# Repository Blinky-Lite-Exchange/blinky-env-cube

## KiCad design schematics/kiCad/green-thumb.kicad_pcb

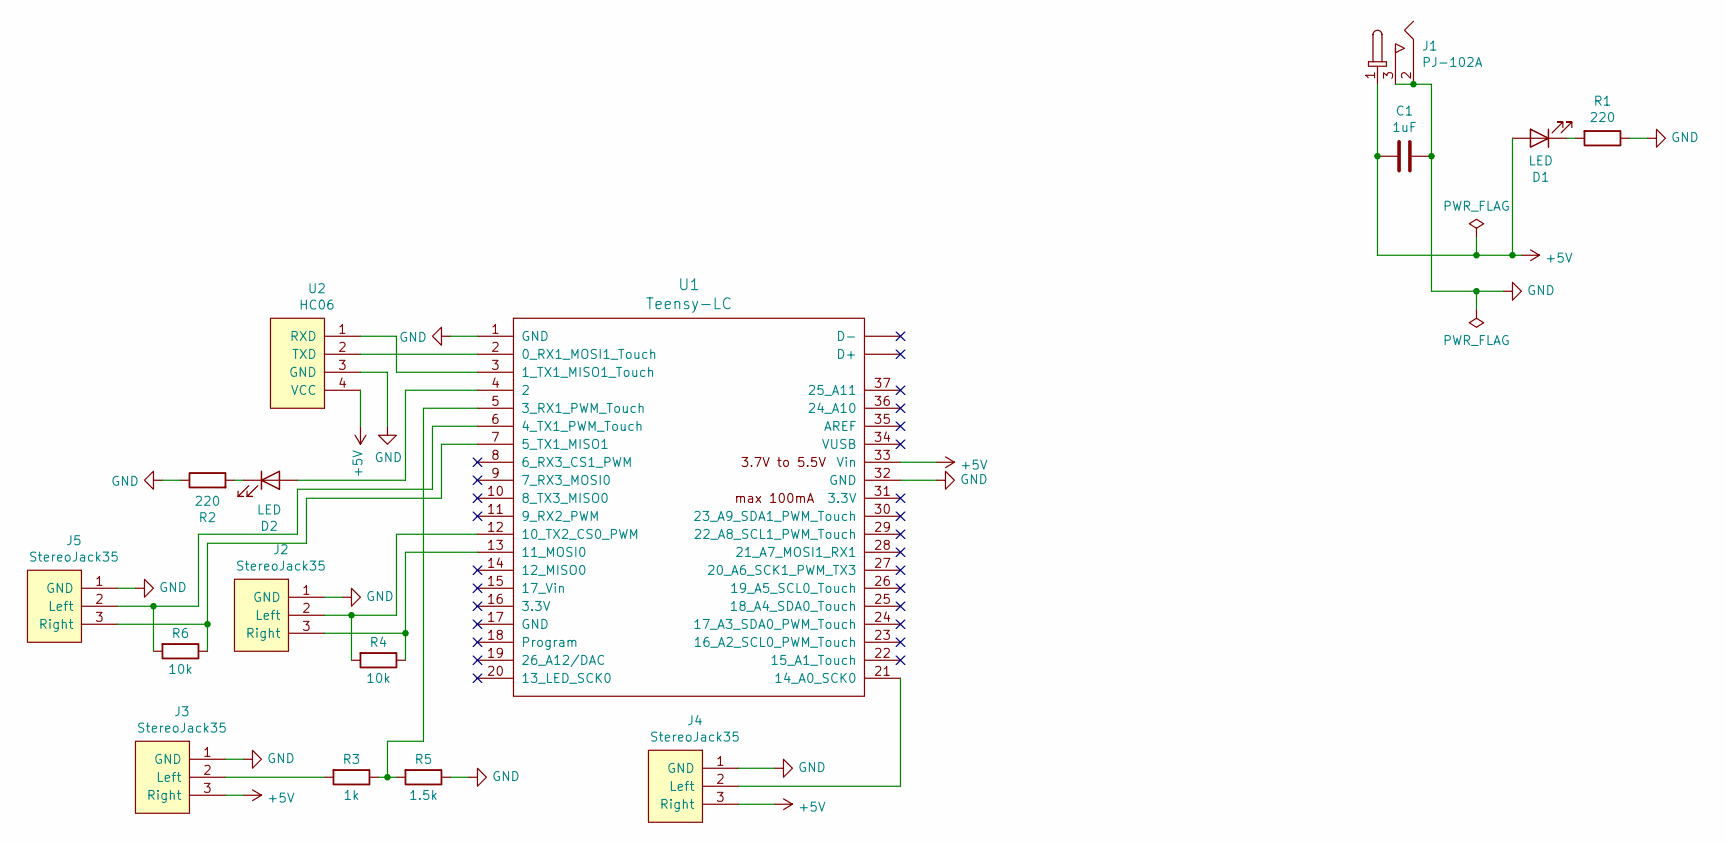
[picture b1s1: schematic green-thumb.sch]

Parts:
C1: 1uF; C_1206_3216Metric_Pad1.42x1.75mm_HandSolder
D1, D2: LED; LED_D5.0mm
J1: PJ-102A; DC21Jack
J2, J3, J4, J5: StereoJack35
R1, R2: 220; R_1206_3216Metric_Pad1.42x1.75mm_HandSolder
R3: 1k; R_1206_3216Metric_Pad1.42x1.75mm_HandSolder
R4, R6: 10k; R_1206_3216Metric_Pad1.42x1.75mm_HandSolder
R5: 1.5k; R_1206_3216Metric_Pad1.42x1.75mm_HandSolder
U1: Teensy-LC; Teensy30_31_32_LC
U2: HC06

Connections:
+5V: C1.2, D1.2 (A), J1.1, J3.3 (Right), J4.3 (Right), U1.33 (Vin), U2.4 (VCC)
GND: C1.1, J1.2, J1.3, J2.1 (GND), J3.1 (GND), J4.1 (GND), J5.1 (GND), R1.1, R2.1, R5.1, U1.1 (GND), U1.32 (GND), U2.3 (GND)
unnamed: D1.1 (K), R1.2
unnamed: D2.1 (K), R2.2
unnamed: D2.2 (A), U1.4 (2)
unnamed: J2.2 (Left), R4.2, U1.12 (10_TX2_CS0_PWM)
unnamed: J2.3 (Right), R4.1, U1.13 (11_MOSI0)
unnamed: J3.2 (Left), R3.2
unnamed: J4.2 (Left), U1.21 (14_A0_SCK0)
unnamed: J5.2 (Left), R6.2, U1.6 (4_TX1_PWM_Touch)
unnamed: J5.3 (Right), R6.1, U1.7 (5_TX1_MISO1)
unnamed: R3.1, R5.2, U1.5 (3_RX1_PWM_Touch)
unnamed: U1.2 (0_RX1_MOSI1_Touch), U2.2 (TXD)
unnamed: U1.3 (1_TX1_MISO1_Touch), U2.1 (RXD)

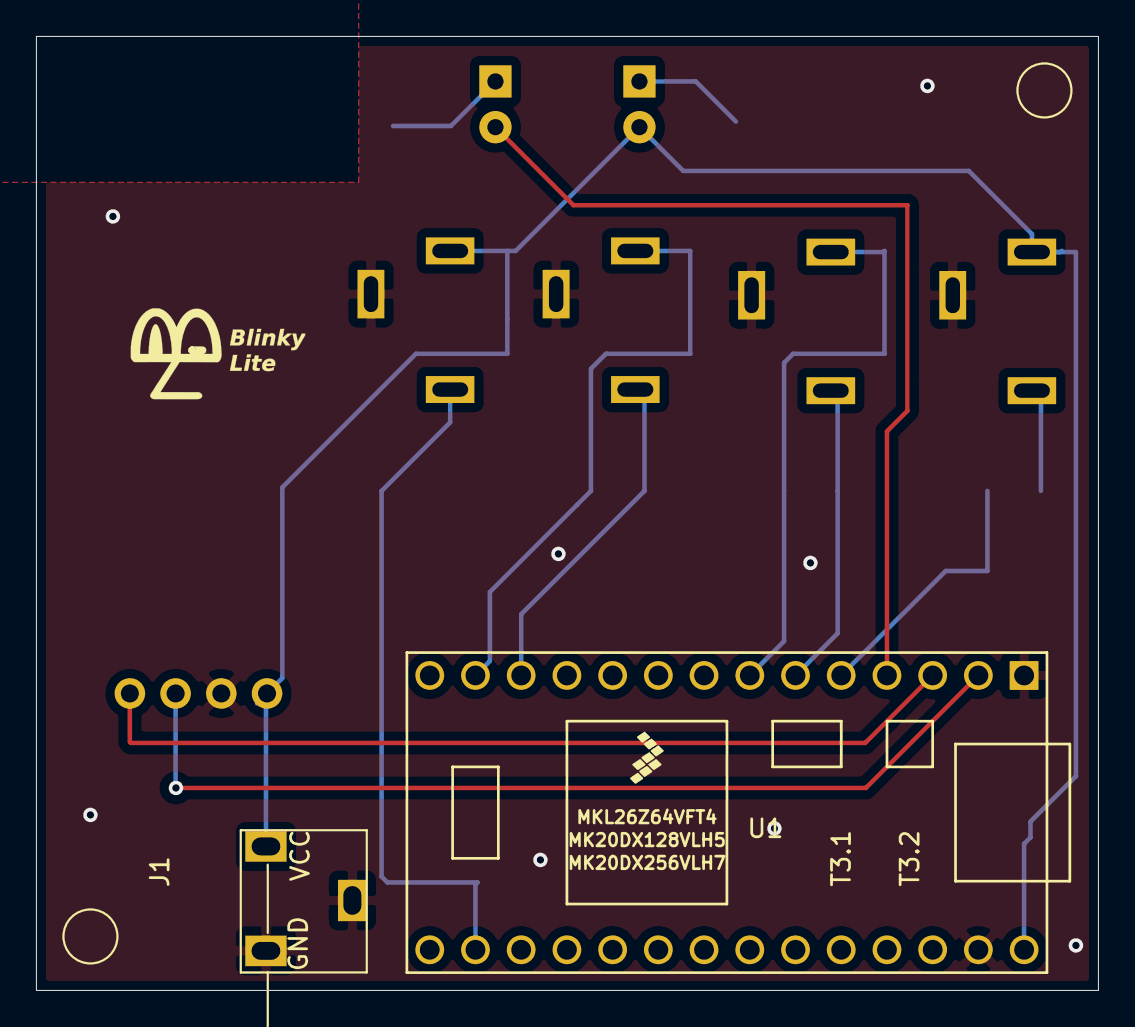
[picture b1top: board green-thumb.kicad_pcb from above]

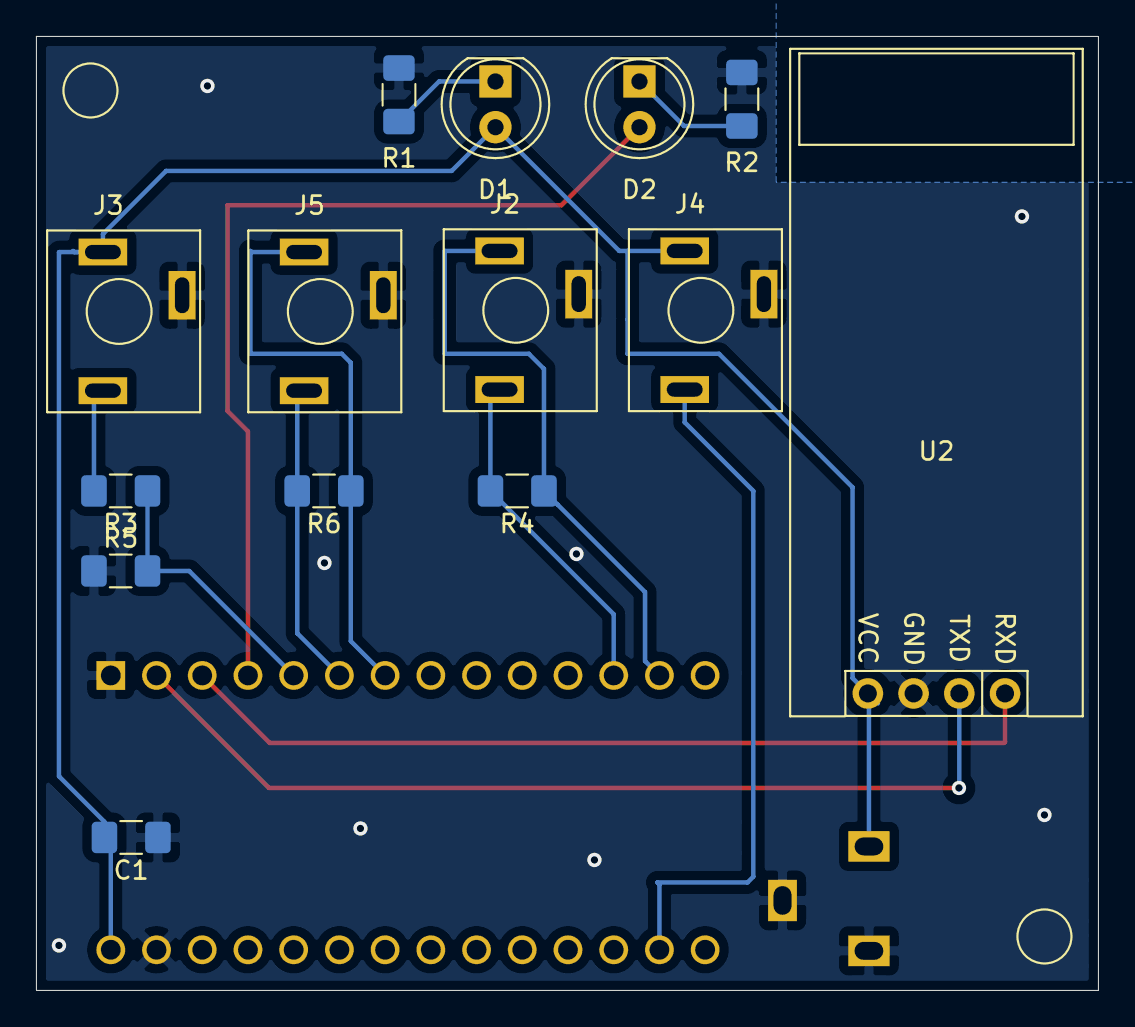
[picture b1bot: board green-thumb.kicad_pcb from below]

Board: 2 copper layers, 59.0 x 53.0 mm, 16 parts (14 on the bottom side), 14 nets.

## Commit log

2020-03-22 working with tray
2020-03-27 added kicad schematics
2022-04-03 switch to bllinky-lite 4
